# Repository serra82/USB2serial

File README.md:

USB2serial
==========

USB to serial converter based on FT232 or MCP2200.
The board has been developed with KiCad.
Is possible to use for TTL levels or RS232 soldering a MAX232.

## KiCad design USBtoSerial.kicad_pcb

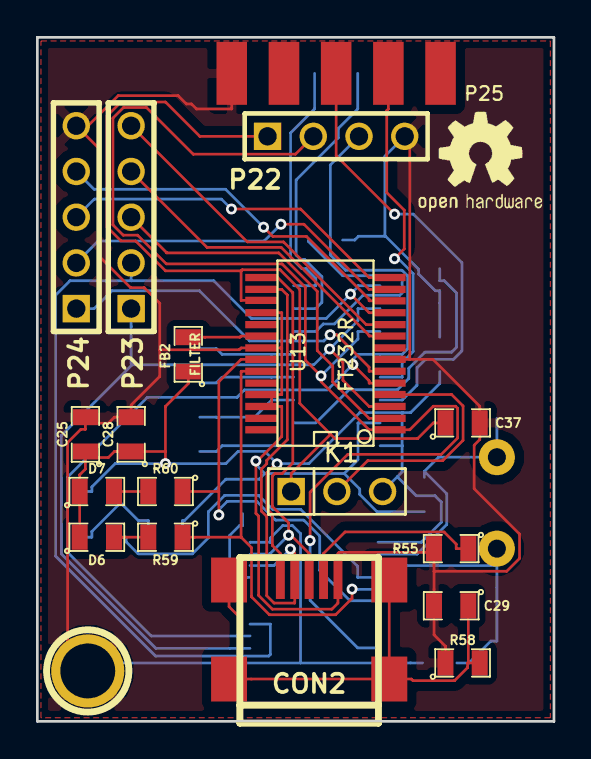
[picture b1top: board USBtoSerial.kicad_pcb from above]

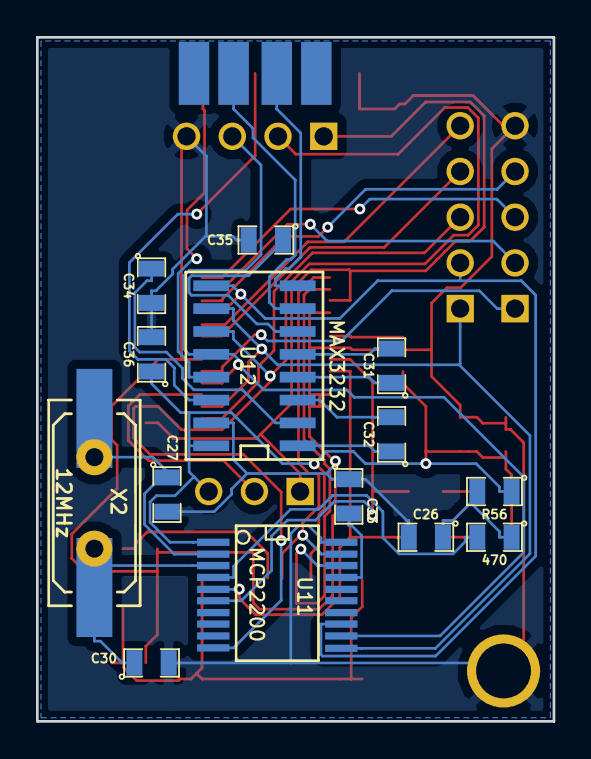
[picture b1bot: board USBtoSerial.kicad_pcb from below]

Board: 2 copper layers, 28.7 x 38.0 mm, 33 parts (14 on the bottom side), 39 nets.

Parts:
C25: 4,7uF; SM0805
C26, C36: 0.1uF; SM0805
C27, C30: 16pF; SM0805
C28, C37: 100nF; SM0805
C29: 10n 500V; SM0805
C31, C34, C35: 0.33uF; SM0805
C32: 0.047uF; SM0805
C33: 470nF; SM0805
CON2: USB-MINI-B; USB_MINI_B_2Hole
D6: KPT-1608 EC; SM0805
D7: KPT-1608 YC; SM0805
FB2: FILTER; SM0805
K1: CONN_3; PIN_ARRAY_3X1
P1: CONN_1; 1pin
P22: CONN_4; PIN_ARRAY_4x1
P23, P24: CONN_5; PIN_ARRAY_5x1
P25: CONN_9; DB9_smd
R55: R; SM0805
R56: 10K; SM0805
R57: 470; SM0805
R58: 1M; SM0805
R59, R60: 330; SM0805
U11: MCP2200; SSOP20big
U12: MAX3232; SOIC16
U13: FT232R; SSOP28big
X2: 12MHz; Q_49U3HMS_hole

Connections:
CBUS2: P24.2, U13.13
CBUS3: P24.3, U13.14
CBUS4: P24.4, U13.12
CTS: P23.2, U11.13, U12.9, U13.11
CTS_DB9: P25.8, U12.8
D+: CON2.3, U11.19, U13.15
D-: CON2.2, U11.18, U13.16
DCD: P23.5, U13.10
DSR: P23.4, U13.9
DTR: P23.3, U13.2
FTDI3V3: C37.1, K1.1, P22.1, U13.17
unnamed: D7.2, R60.2
unnamed: D6.2, R59.2
unnamed: C26.1, R56.2, R57.1
unnamed: R57.2, U11.4
unnamed: C35.1, U12.6
unnamed: C31.2, U12.5
unnamed: C31.1, U12.4
unnamed: C32.1, U12.1
unnamed: C32.2, U12.3
unnamed: C34.1, U12.2
unnamed: CON2.4, R55.1
unnamed: C29.1, CON2.6, CON2.7, CON2.8, CON2.9, R58.2
unnamed: C33.2, U11.17
unnamed: FB2.2, U13.20
OSCI1: C27.1, U11.2, X2.1
OSCI2: C30.1, U11.3, X2.2
RI: P24.1, U13.6
RTS: P23.1, U11.11, U12.10, U13.3
RTS_DB9: P25.7, U12.7
RX: P22.3, U11.12, U12.12, U13.5
RXLED: R60.1, U11.6, U13.22
RX_DB9: P25.2, U12.13
TX: P22.2, U11.10, U12.11, U13.1
TXLED: R59.1, U11.5, U13.23
TX_DB9: P25.3, U12.14
USB_GND: C25.2, C26.2, C27.2, C28.2, C29.2, C30.2, C33.1, C34.2, C35.2, C36.2, C37.2, CON2.5, P1.1, P22.4, P24.5, P25.5, R55.2, R58.1, U11.20, U12.15, U13.7, U13.18, U13.21, U13.25, U13.26
VBUS: C25.1, C28.1, C36.1, CON2.1, D6.1, D7.1, FB2.1, K1.3, R56.1, U11.1, U12.16
VCCIO: K1.2, U13.4
